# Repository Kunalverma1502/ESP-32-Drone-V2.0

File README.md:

# ESP-32-Drone-V2.0
ESP32 based mini drone

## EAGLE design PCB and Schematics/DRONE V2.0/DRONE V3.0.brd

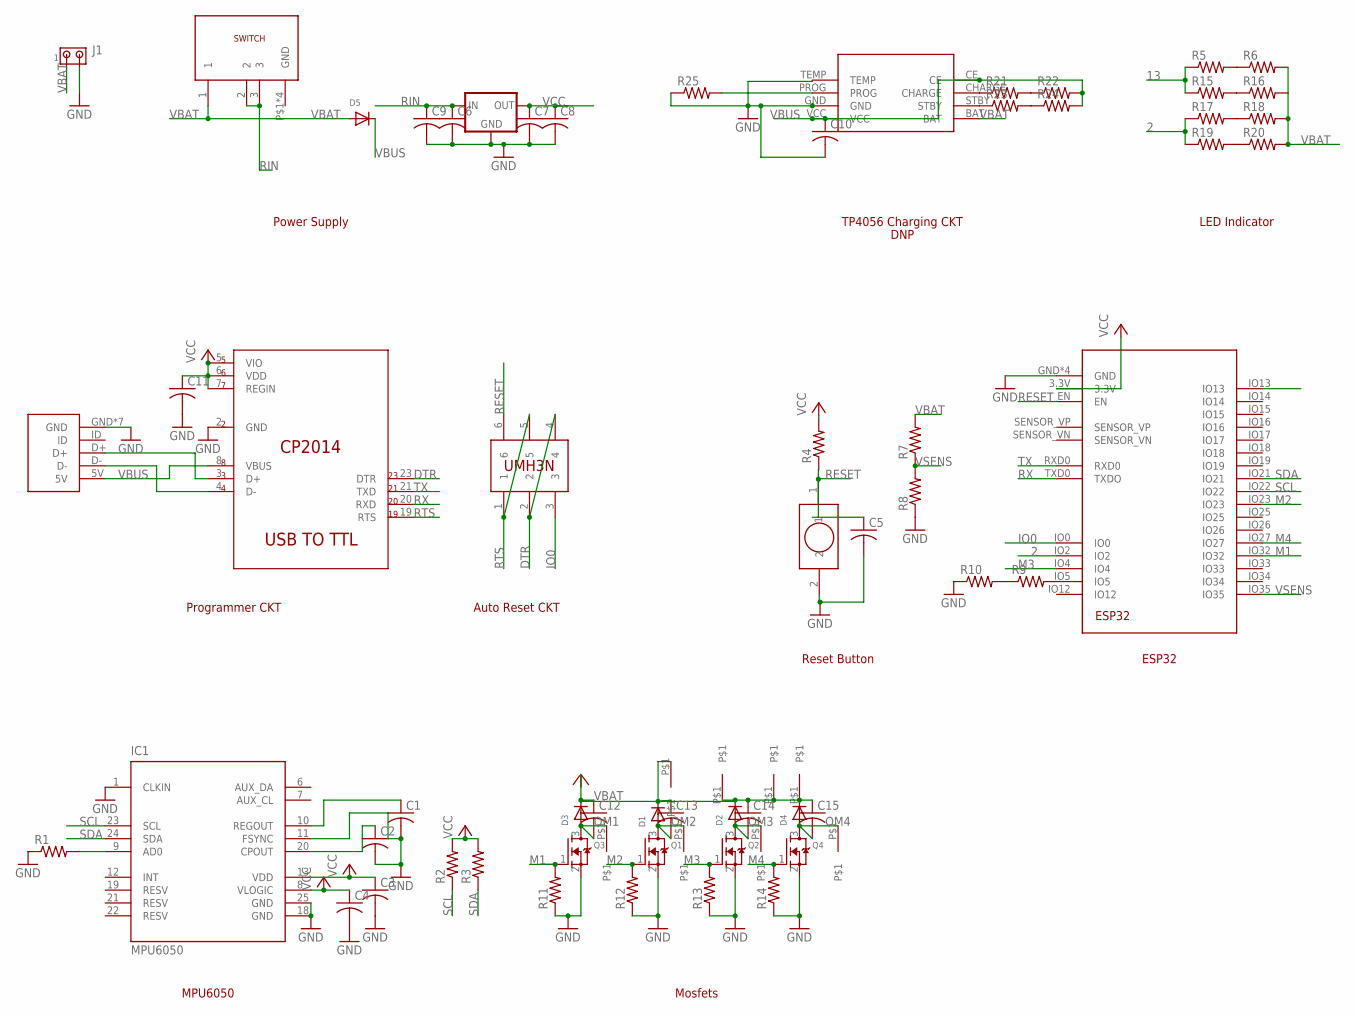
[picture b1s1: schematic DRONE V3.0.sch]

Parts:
C1, C2, C3, C4, C5, C6, C7, C8, C9, C10, C11, C12, C13, C14, C15: C-USC0603; C0603
D1, D2, D3, D4, D5: DIODESOD-323F; SOD-323F
IC1: MPU6050; QFN50P400X400X95-25T265X275N
IC2: V_REG1.8MP; SOT223
J1: MTA02-100; 10X02MTA
Q1, Q2, Q3, Q4: MOSFET-NREFLOW; SOT23
R1, R2, R3, R4, R5, R6, R7, R8, R9, R10, R11, R12, R13, R14, R15, R16, R17, R18, R19, R20, R21, R22, R23, R24, R25: R-US_R0603; R0603
U1: ESP32; MODULE_ESP-WROOM-32
U2: CP2104-F03-GM; QFN50P400X400X80-25N
U$1: MICROUSB; USB
U$2: SELF_PUSHBUTTON
U$3: SWITCH
U$4: TP4056
U$6: UMH3N
U$7, U$8, U$9, U$10, U$11, U$12, U$13, U$14: PINOUTS

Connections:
2: R17.1, R19.1, U1.IO2
13: R5.1, R15.1, U1.IO13
DTR: U2.23 (DTR), U$6.2, U$6.4
GND: C1.2, C2.2, C3.2, C4.2, C5.2, C6.2, C7.2, C8.2, C9.2, C10.2, C11.2, IC1.1 (CLKIN), IC1.11 (FSYNC), IC1.18 (GND), IC1.25 (GND), IC2.GND, J1.2, Q1.2 (S), Q2.2 (S), Q3.2 (S), Q4.2 (S), R1.1, R8.1, R10.1, R11.1, R12.1, R13.1, R14.1, R25.1, U1.GND, U1.GND1 (GND), U1.GND2 (GND), U1.GND3 (GND), U2.2 (GND), U$1.GND, U$1.GND1 (GND), U$1.GND2 (GND), U$1.GND3 (GND), U$1.GND4 (GND), U$1.GND5 (GND), U$1.GND6 (GND), U$2.2, U$4.GND, U$4.TEMP
IO0: U1.IO0, U$6.3
M1: Q3.1 (G), R11.2, U1.IO32
M2: Q1.1 (G), R12.2, U1.IO23
M3: Q2.1 (G), R13.2, U1.IO4
M4: Q4.1 (G), R14.2, U1.IO27
unnamed: IC1.9 (AD0), R1.2
unnamed: R5.2, R6.1
unnamed: R15.2, R16.1
unnamed: C1.1, IC1.10 (REGOUT)
unnamed: C2.1, IC1.20 (CPOUT)
unnamed: U2.3 (D+), U$1.D+
unnamed: U2.4 (D-), U$1.D-
unnamed: R9.2, U1.IO5
unnamed: R9.1, R10.2
unnamed: R17.2, R18.1
unnamed: R19.2, R20.1
unnamed: R21.1, U$4.CHARGE
unnamed: R21.2, R22.1
unnamed: R23.1, U$4.STBY
unnamed: R23.2, R24.1
unnamed: R25.2, U$4.PROG
OM1: C12.2, D3.A, Q3.3 (D), U$12.P$1
OM2: C13.2, D1.A, Q1.3 (D), U$8.P$1
OM3: C14.2, D2.A, Q2.3 (D), U$10.P$1
OM4: C15.2, D4.A, Q4.3 (D), U$13.P$1
RESET: C5.1, R4.1, U1.EN, U$2.1, U$6.6
RIN: C6.1, C9.1, IC2.VIN (IN), U$3.2, U$3.3
RTS: U2.19 (RTS), U$6.1, U$6.5
RX: U1.TXD0 (TXDO), U2.20 (RXD)
SCL: IC1.23 (SCL), R2.1, U1.IO22
SDA: IC1.24 (SDA), R3.1, U1.IO21
TX: U1.RXD0, U2.21 (TXD)
VBAT: C12.1, C13.1, C14.1, C15.1, D1.C, D2.C, D3.C, D4.C, D5.A, J1.1, R6.2, R7.2, R16.2, R18.2, R20.2, U$3.1, U$4.BAT, U$7.P$1, U$9.P$1, U$11.P$1, U$14.P$1
VBUS: C10.1, D5.C, R22.2, R24.2, U2.8 (VBUS), U$1.5V, U$4.CE, U$4.VCC
VCC: C3.1, C4.1, C7.1, C8.1, C11.1, IC1.8 (VLOGIC), IC1.13 (VDD), IC2.VOUT (OUT), IC2.VOUT1 (OUT), R2.2, R3.2, R4.2, U1.3.3V, U2.5 (VIO), U2.6 (VDD), U2.7 (REGIN)
VSENS: R7.1, R8.2, U1.IO35

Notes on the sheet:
Power Supply
TP4056 Charging CKT
DNP
LED Indicator
Programmer CKT
Auto Reset CKT
Reset Button
ESP32
MPU6050
Mosfets

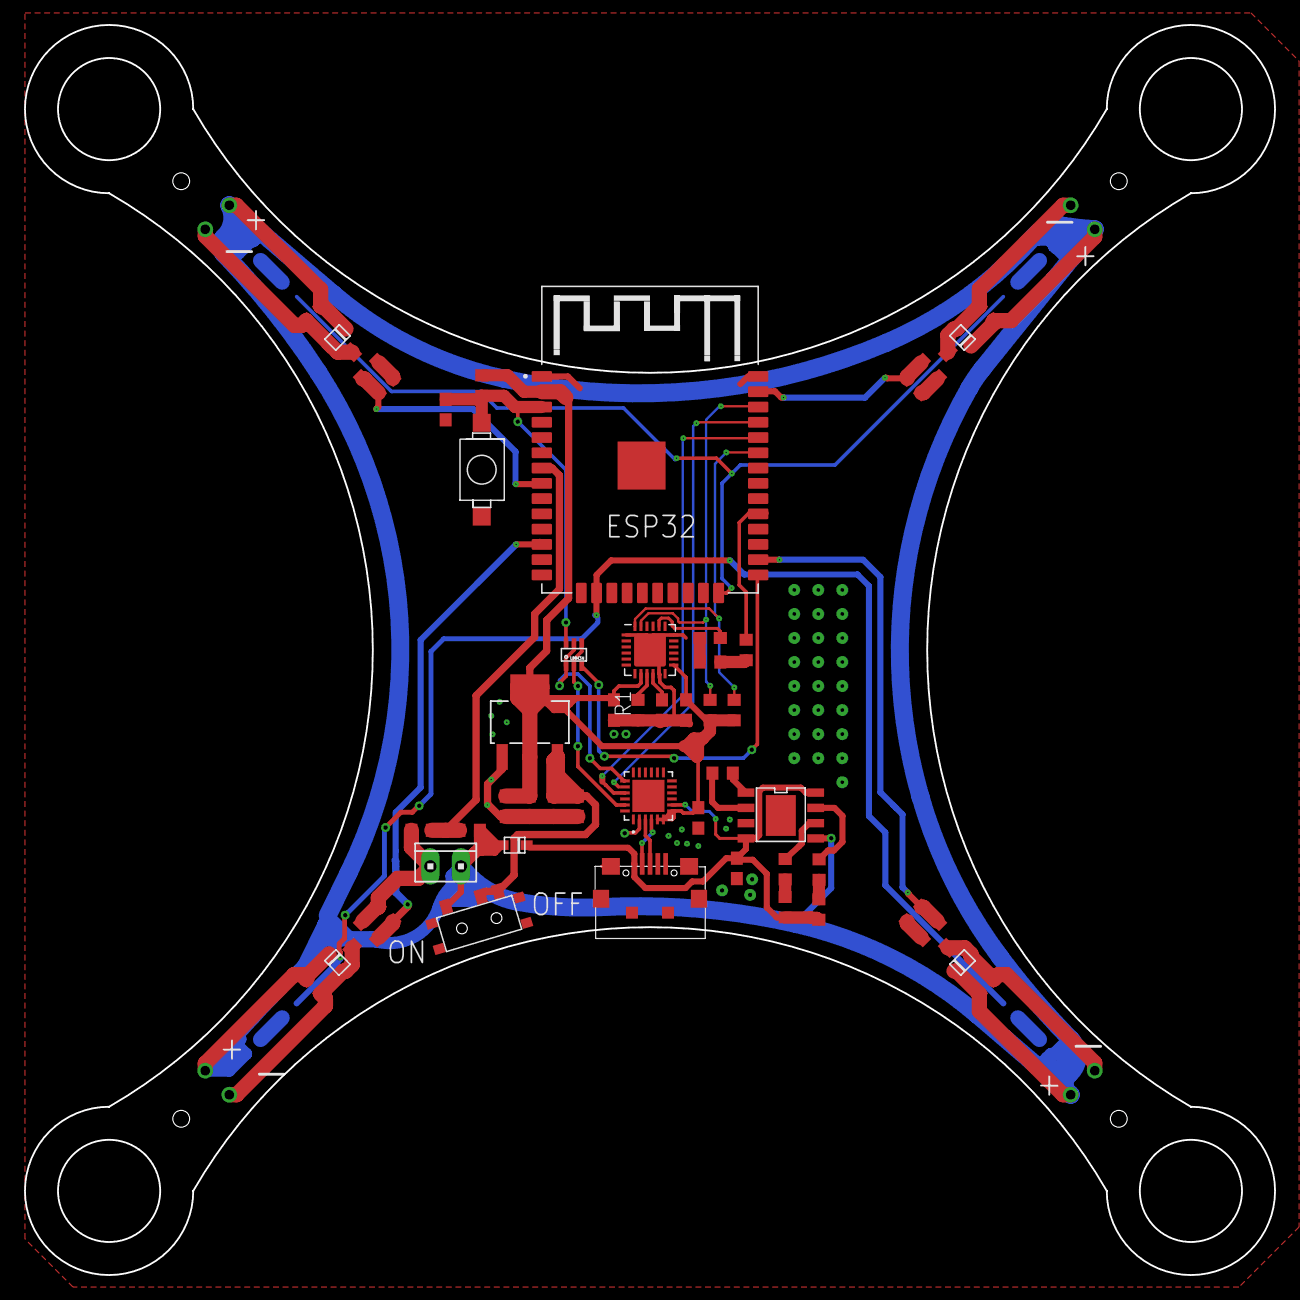
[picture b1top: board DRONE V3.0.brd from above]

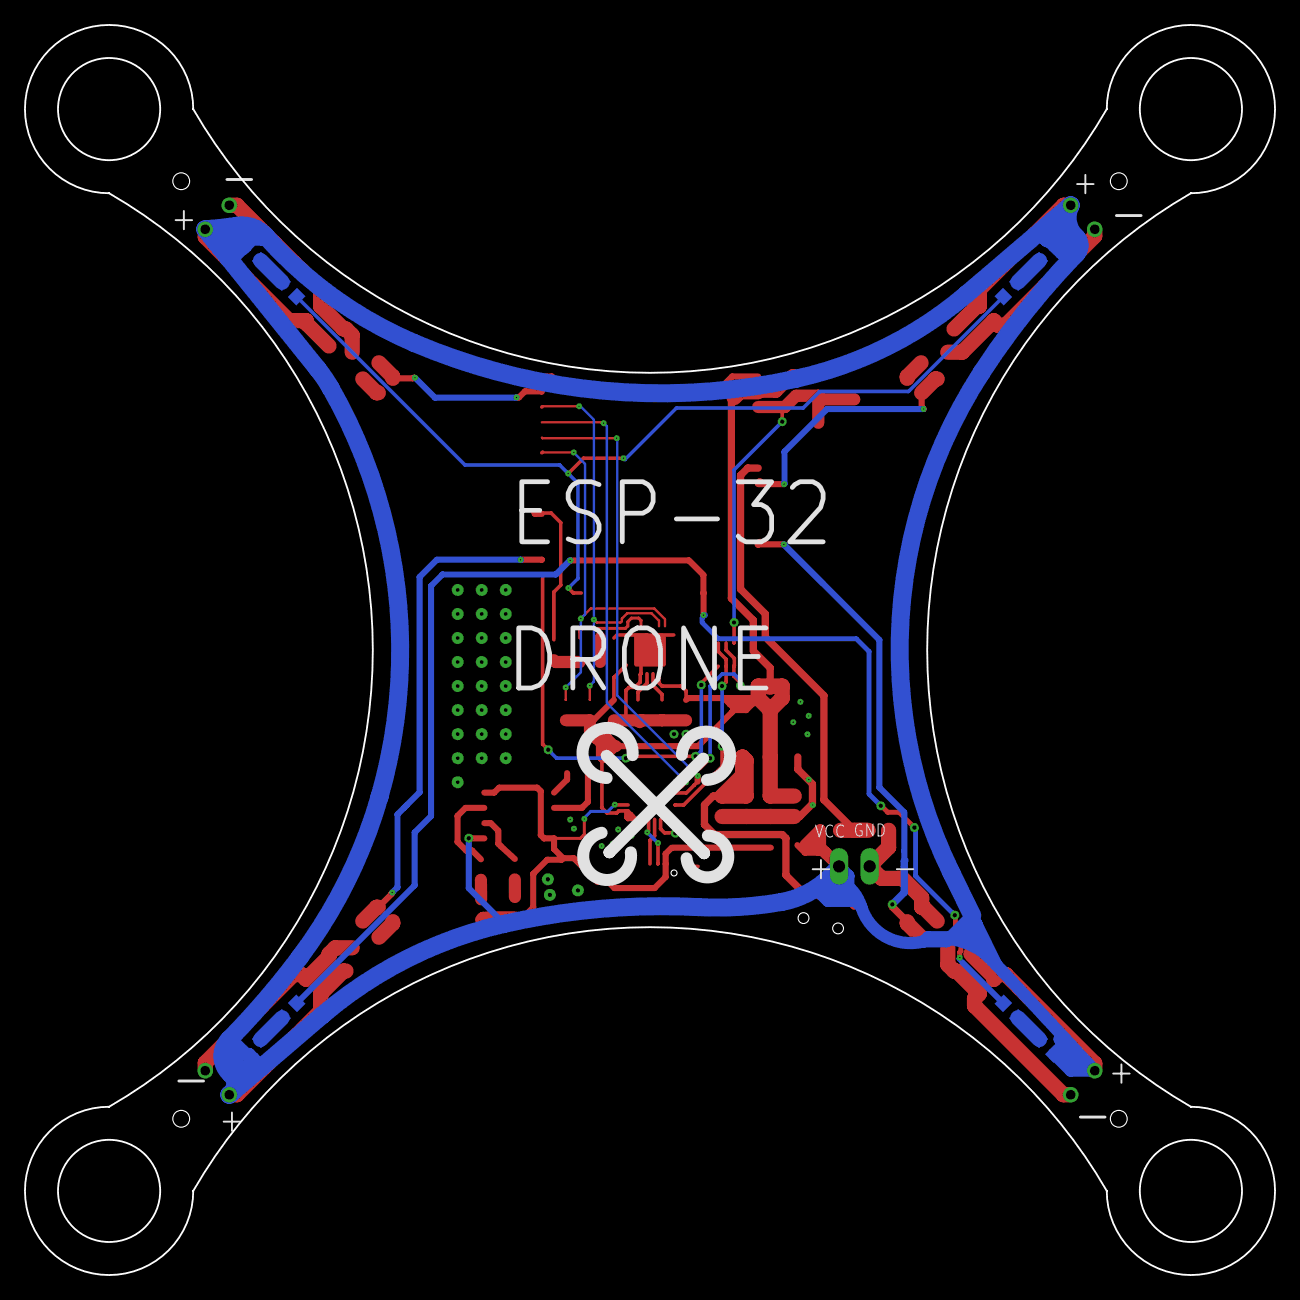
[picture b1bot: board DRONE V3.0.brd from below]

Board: 2 copper layers, 104.0 x 104.0 mm, 67 parts (8 on the bottom side), 40 nets.

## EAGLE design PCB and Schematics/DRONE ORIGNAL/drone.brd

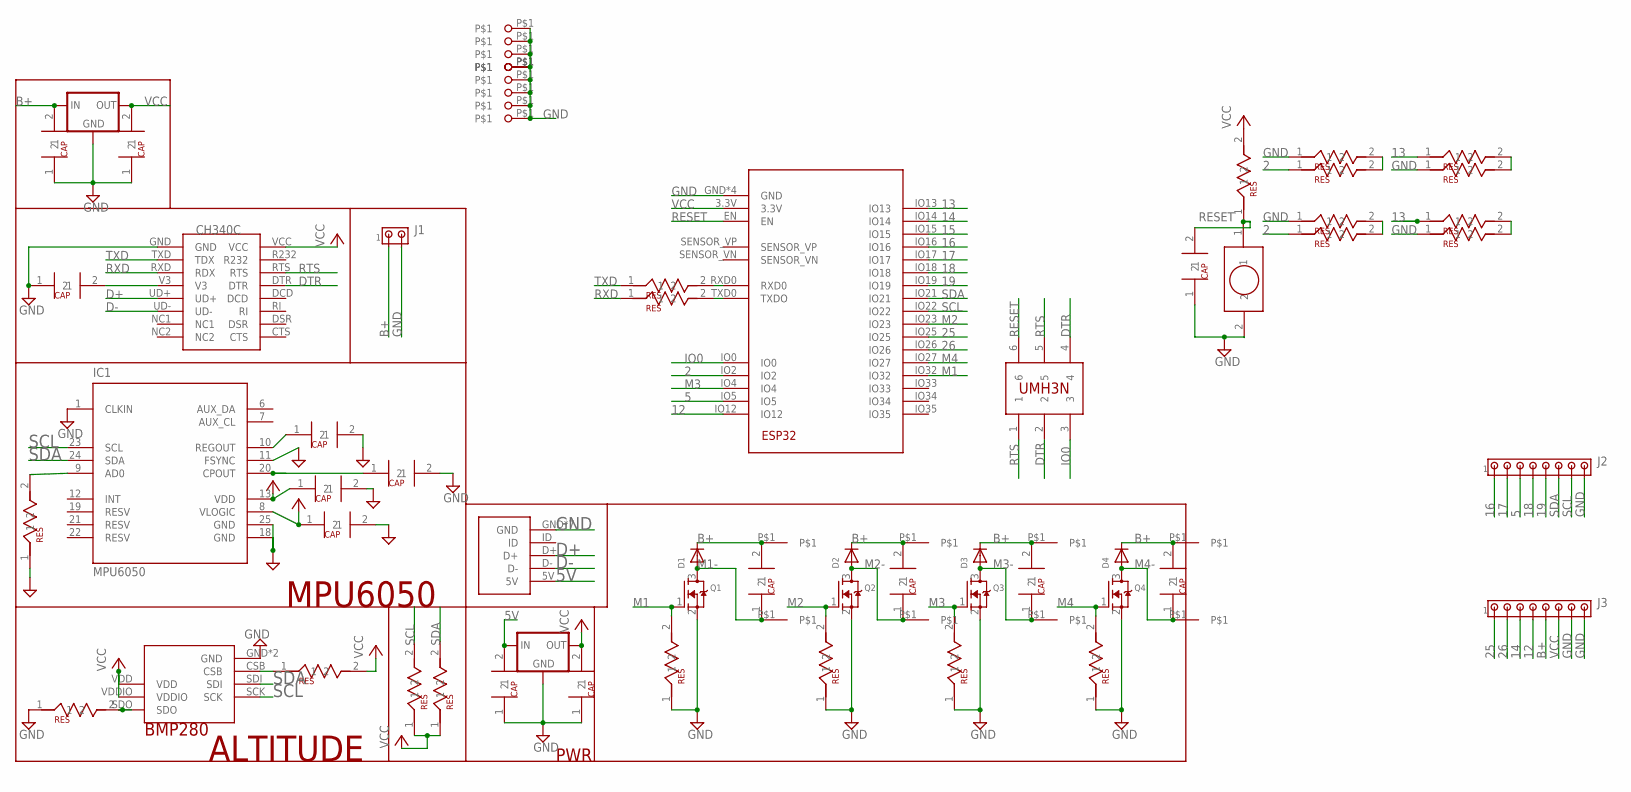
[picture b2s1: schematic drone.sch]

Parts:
D1, D2, D3, D4: DIODESOD-323F; SOD-323F
IC1: MPU6050; QFN50P400X400X95-25T265X275N
IC2, IC3: SELF_VREG3.3MP; SOT223
J1: MTA02-100; 10X02MTA
J2, J3: MTA08-100; 10X08MTA
Q1, Q2, Q3, Q4: MOSFET-NREFLOW; SOT23
U1: ESP32; MODULE_ESP-WROOM-32
U$1: MICROUSB; USB
U$2: CH340C; SOIC16
U$3: BMP280
U$4, U$5, U$7, U$11, U$12, U$16, U$17, U$20, U$21, U$22, U$23, U$30, U$32, U$33, U$34, U$35, U$36, U$37, U$38, U$39: SELF_RESISTOR_0603
U$6, U$8, U$9, U$10, U$15, U$24, U$25, U$26, U$27, U$31: SELF_CAP_0603
U$13, U$14, U$18, U$19: SELF_CAP_0603SELF_CAP_0805; SELF_CAP_0805
U$28: UMH3N
U$29: SELF_PUSHBUTTON
U$40, U$41, U$42, U$43, U$44, U$45, U$46, U$47: SELF_PINOUTS; PINOUTS
U$48, U$49, U$50, U$51, U$52, U$53, U$54, U$55, U$56: SELF_PIN2; PIN2

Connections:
2: U1.IO2, U$33.1, U$39.1
5: J2.3, U1.IO5
5V: IC2.VIN (IN), U$1.5V, U$13.2
12: J3.4, U1.IO12
13: U1.IO13, U$34.1, U$36.1
14: J3.3, U1.IO14
15: U1.IO15
16: J2.1, U1.IO16
17: J2.2, U1.IO17
18: J2.4, U1.IO18
19: J2.5, U1.IO19
25: J3.1, U1.IO25
26: J3.2, U1.IO26
B+: D1.C, D2.C, D3.C, D4.C, IC3.VIN (IN), J1.1, J3.5, U$19.2, U$24.2, U$25.2, U$26.2, U$27.2, U$40.P$1, U$42.P$1, U$44.P$1, U$46.P$1
D+: U$1.D+, U$2.UD+
D-: U$1.D-, U$2.UD-
DTR: U$2.DTR, U$28.2, U$28.4
GND: IC1.1 (CLKIN), IC1.11 (FSYNC), IC1.18 (GND), IC1.25 (GND), IC2.GND, IC3.GND, J1.2, J2.8, J3.7, J3.8, Q1.2 (S), Q2.2 (S), Q3.2 (S), Q4.2 (S), U1.GND, U1.GND1 (GND), U1.GND2 (GND), U1.GND3 (GND), U$1.GND, U$1.GND1 (GND), U$1.GND2 (GND), U$1.GND3 (GND), U$1.GND4 (GND), U$1.GND5 (GND), U$1.GND6 (GND), U$2.GND, U$3.GND, U$3.GND1 (GND), U$5.1, U$6.2, U$7.1, U$8.2, U$9.2, U$10.2, U$13.1, U$14.1, U$15.1, U$18.1, U$19.1, U$20.1, U$21.1, U$22.1, U$23.1, U$29.2, U$31.1, U$32.1, U$35.1, U$37.1, U$38.1, U$48.P$1, U$49.P$1, U$50.P$1, U$51.P$1, U$52.P$1, U$53.P$1, U$54.P$1, U$55.P$1, U$56.P$1
IO0: U1.IO0, U$28.3
M1: Q1.1 (G), U1.IO32, U$20.2
M1-: D1.A, Q1.3 (D), U$24.1, U$41.P$1
M2: Q2.1 (G), U1.IO23, U$21.2
M2-: D2.A, Q2.3 (D), U$26.1, U$43.P$1
M3: Q3.1 (G), U1.IO4, U$22.2
M3-: D3.A, Q3.3 (D), U$27.1, U$45.P$1
M4: Q4.1 (G), U1.IO27, U$23.2
M4-: D4.A, Q4.3 (D), U$25.1, U$47.P$1
unnamed: U$32.2, U$33.2
unnamed: U$38.2, U$39.2
unnamed: U$34.2, U$35.2
unnamed: U$36.2, U$37.2
unnamed: U$3.SDO, U$5.2
unnamed: U$3.CSB, U$4.1
unnamed: IC1.9 (AD0), U$7.2
unnamed: IC1.10 (REGOUT), U$8.1
unnamed: IC1.20 (CPOUT), U$10.1
unnamed: U1.RXD0, U$16.2
unnamed: U1.TXD0 (TXDO), U$17.2
unnamed: U$2.V3, U$15.2
RESET: U1.EN, U$28.6, U$29.1, U$30.1, U$31.2
RTS: U$2.RTS, U$28.1, U$28.5
RXD: U$2.RXD (RDX), U$17.1
SCL: IC1.23 (SCL), J2.7, U1.IO22, U$3.SCK, U$11.2
SDA: IC1.24 (SDA), J2.6, U1.IO21, U$3.SDI, U$12.2
TXD: U$2.TXD (TDX), U$16.1
VCC: IC1.8 (VLOGIC), IC1.13 (VDD), IC2.VOUT (OUT), IC2.VOUT1 (OUT), IC3.VOUT (OUT), IC3.VOUT1 (OUT), J3.6, U1.3.3V, U$2.VCC, U$3.VDD, U$3.VDDIO, U$4.2, U$6.1, U$9.1, U$11.1, U$12.1, U$14.2, U$18.2, U$30.2

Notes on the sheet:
ALTITUDE
MPU6050
PWR

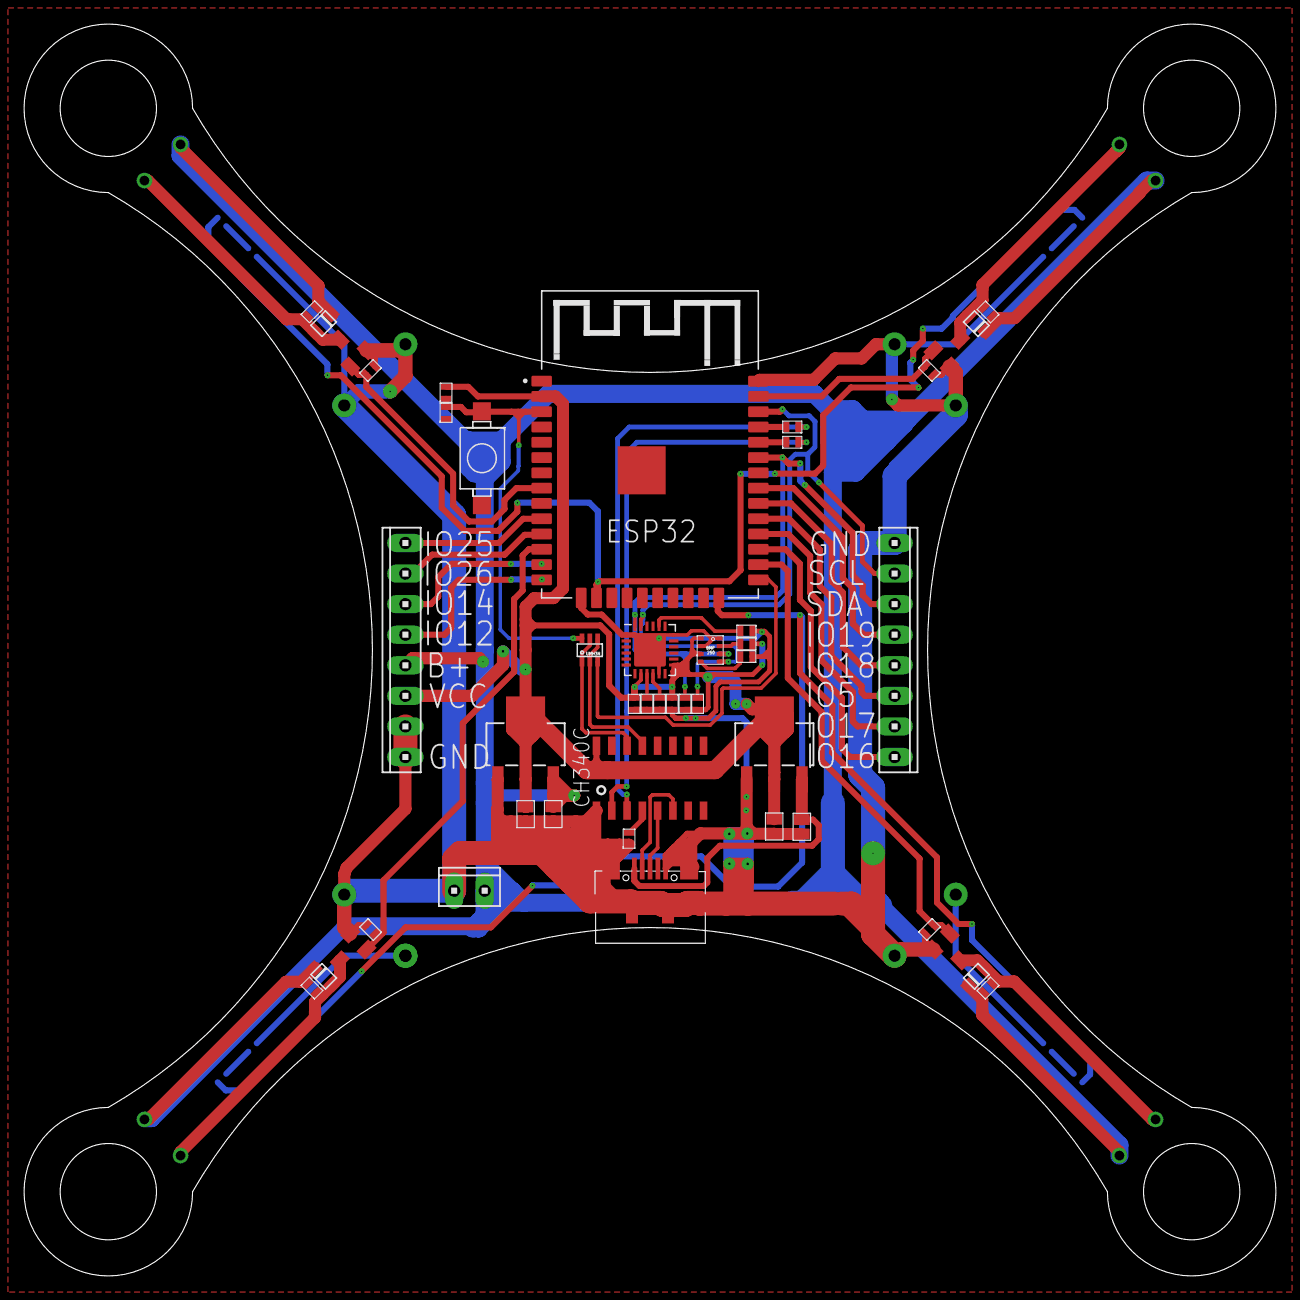
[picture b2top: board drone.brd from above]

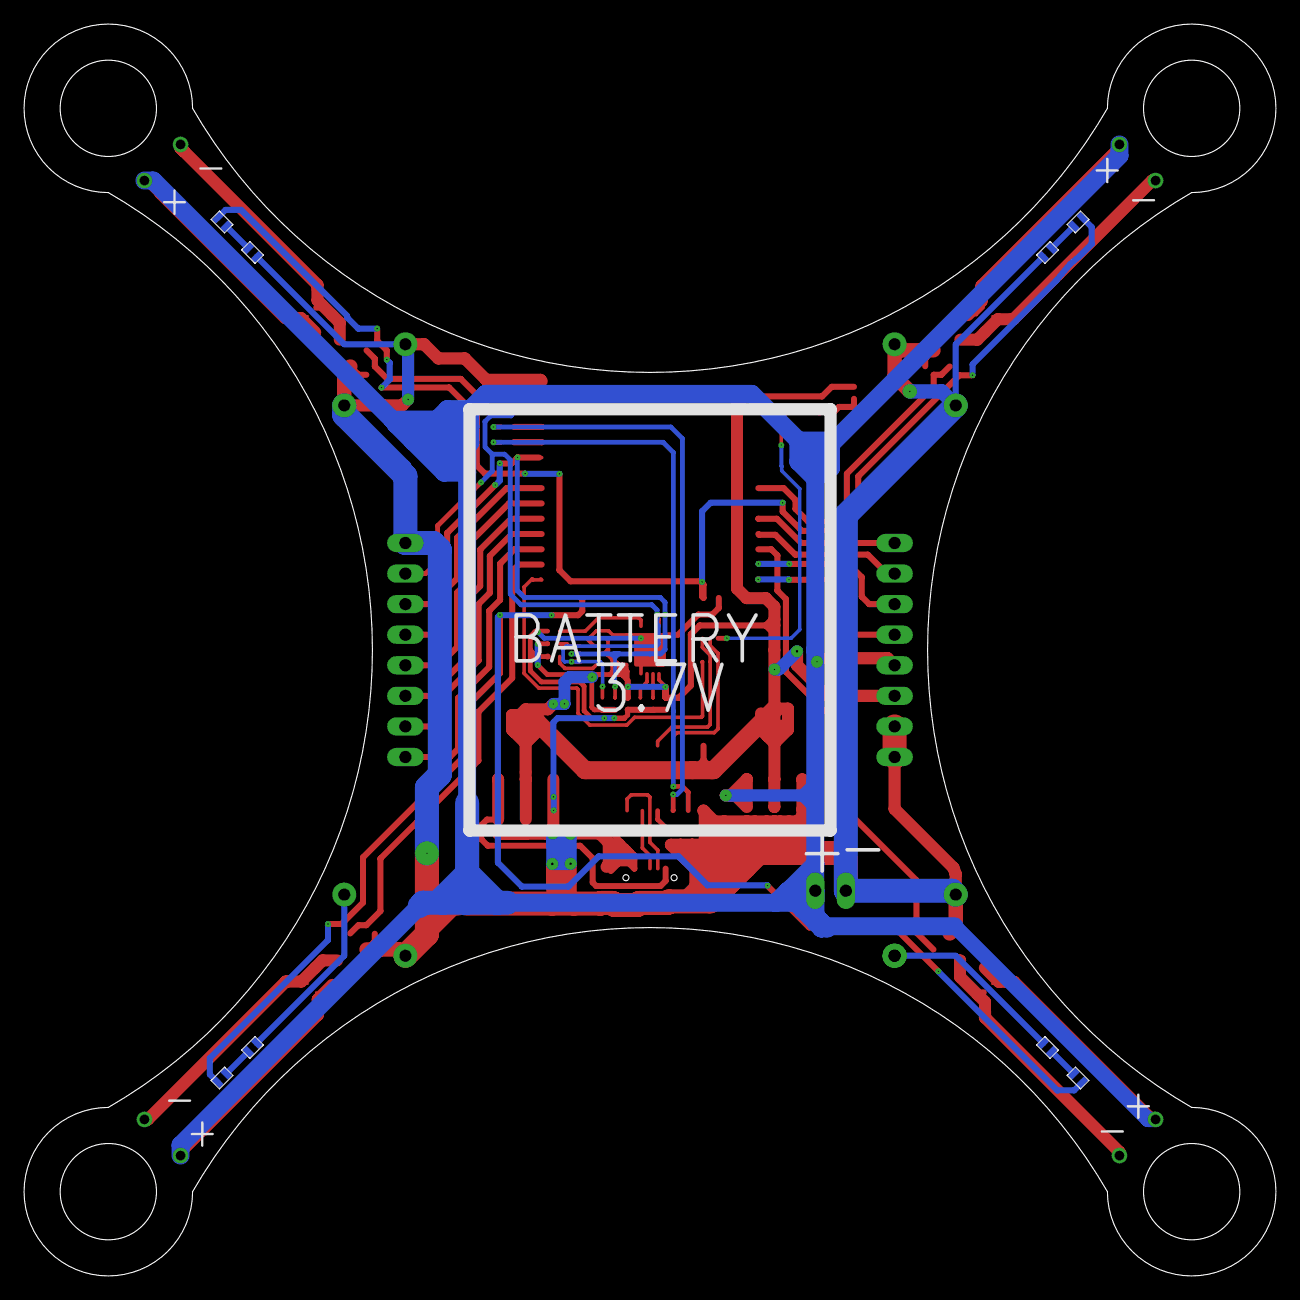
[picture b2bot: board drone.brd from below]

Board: 2 copper layers, 104.0 x 104.0 mm, 71 parts (8 on the bottom side), 45 nets.
